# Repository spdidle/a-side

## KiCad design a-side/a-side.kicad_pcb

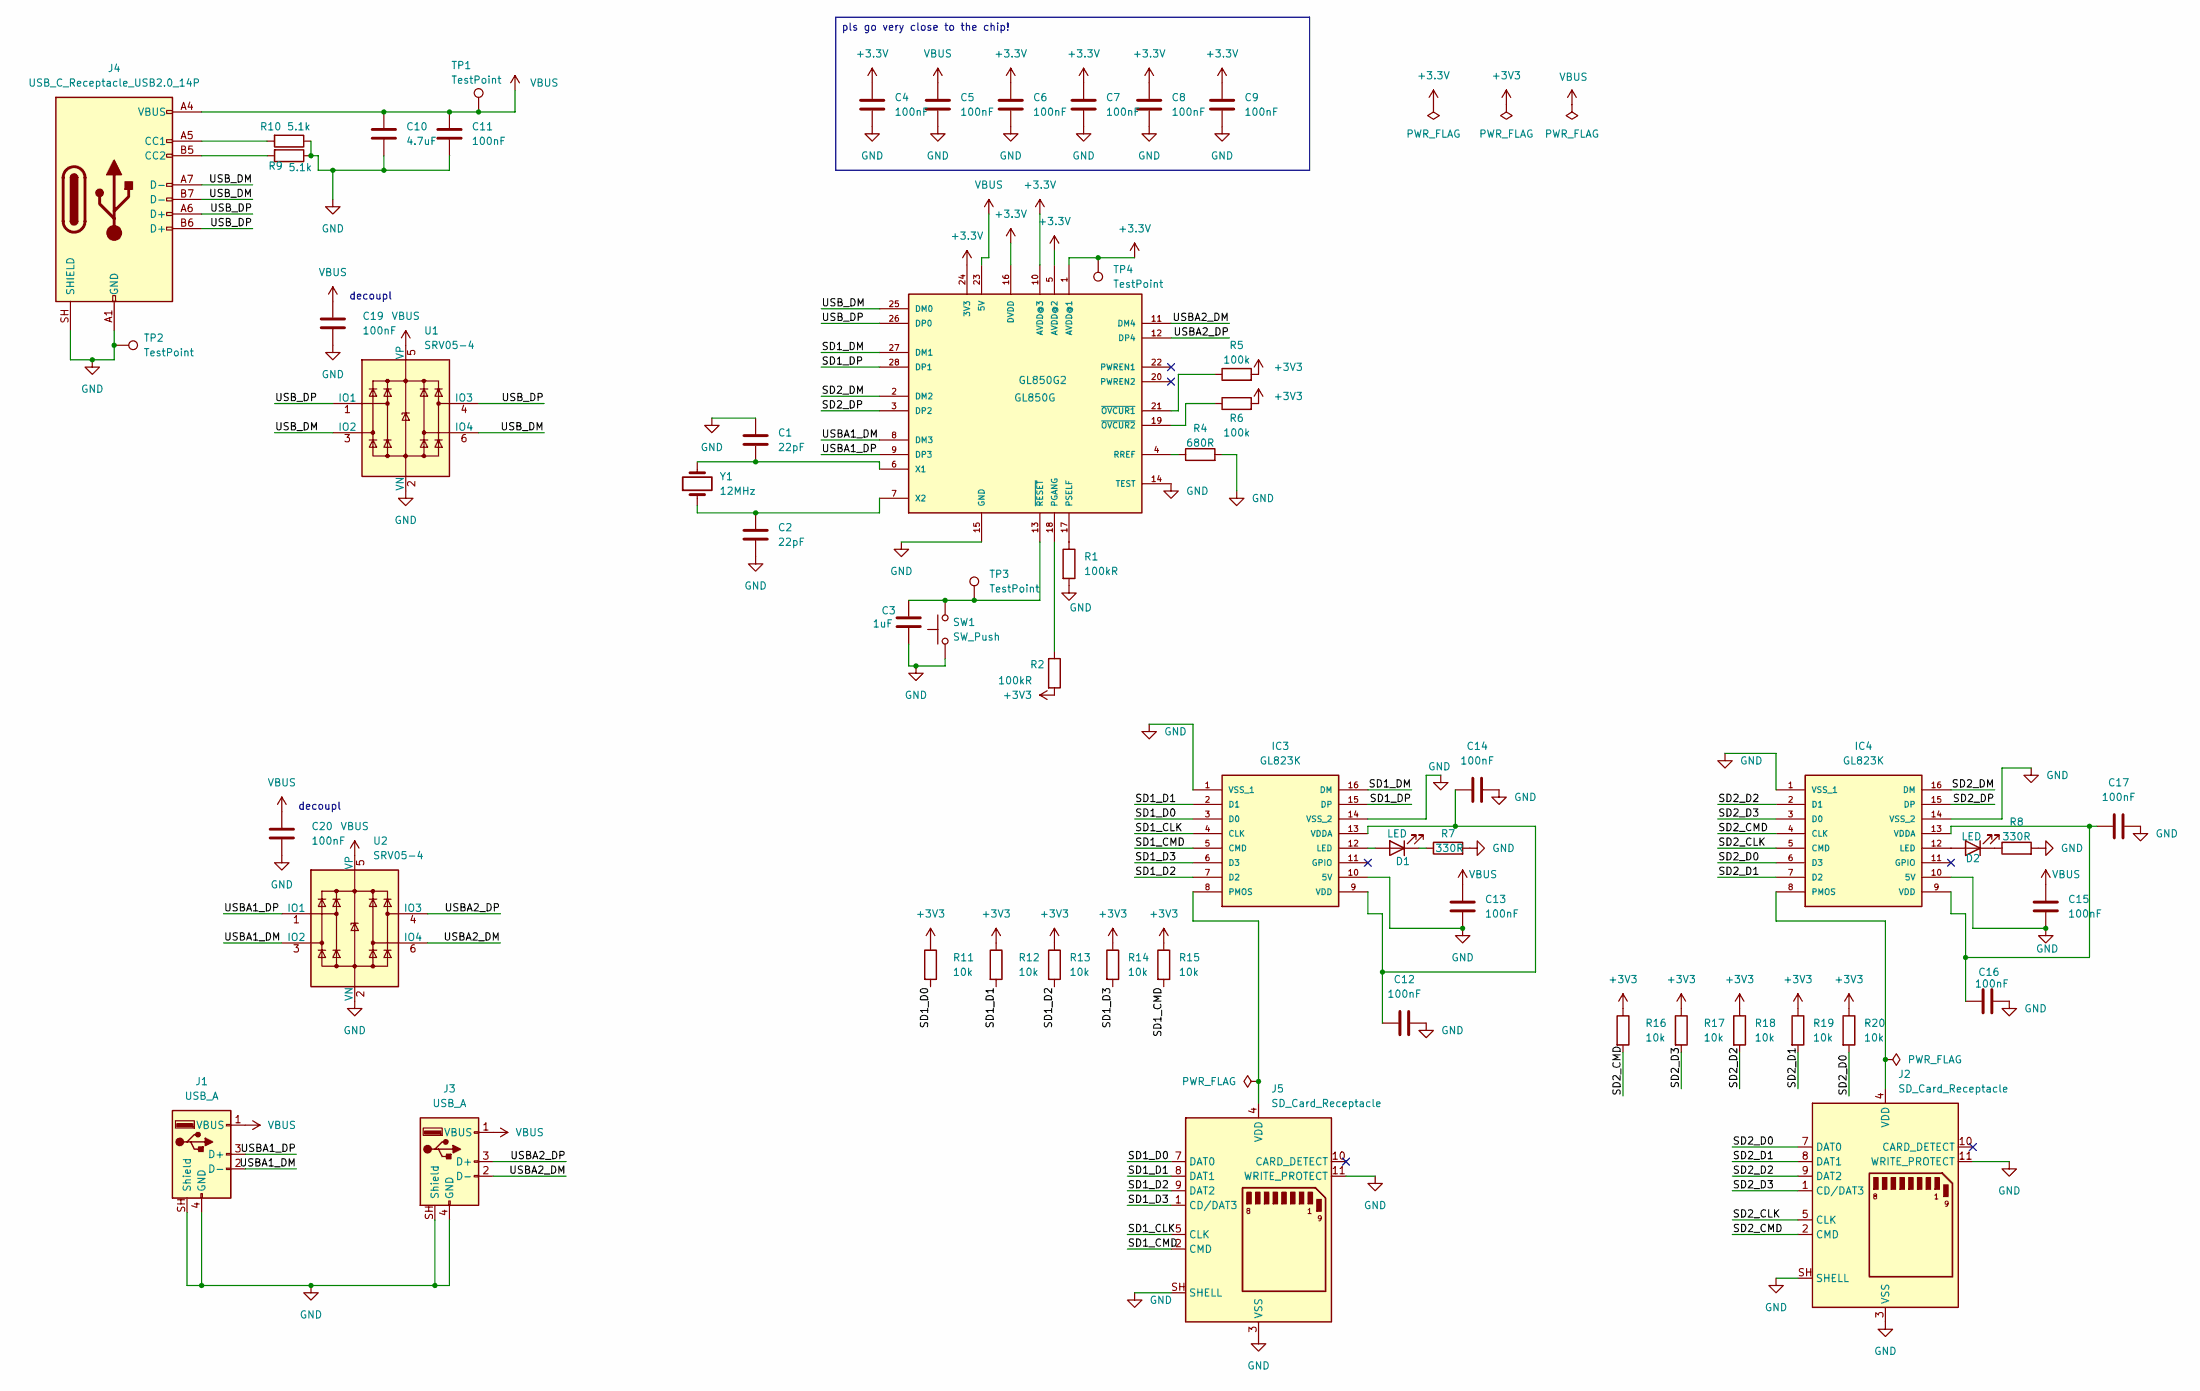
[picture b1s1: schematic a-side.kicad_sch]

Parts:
C1, C2: 22pF; C_0805_2012Metric
C3: 1uF; C_0805_2012Metric
C4, C5, C6, C7, C8, C9, C11, C12, C13, C14, C15, C16, C17, C19, C20: 100nF; C_0805_2012Metric
C10: 4.7uF; C_0805_2012Metric
D1, D2: LED; LED_0805_2012Metric_Pad1.15x1.40mm_HandSolder
GL850G2: GL850G; 28SSOP
IC3, IC4: GL823K; SOP64P600X175-16N; MANUFACTURER_PART_NUMBER GL823K
J1, J3: USB_A; USB_A_Connfly_DS1098_Horizontal
J2, J5: SD_Card_Receptacle; SD_Kyocera_145638009511859+
J4: USB_C_Receptacle_USB2.0_14P; USB_C_Receptacle_HRO_TYPE-C-31-M-12
R1, R2: 100kR; R_0805_2012Metric
R4: 680R; R_0805_2012Metric
R5, R6: 100k; R_0805_2012Metric
R7, R8: 330R; R_0805_2012Metric
R9, R10: 5.1k; R_0805_2012Metric
R11, R12, R13, R14, R15, R16, R17, R18, R19, R20: 10k; R_0805_2012Metric
SW1: SW_Push; SW_Push_SPST_NO_Alps_SKRK
TP1, TP2, TP3, TP4: TestPoint; TestPoint_Pad_D1.0mm
U1, U2: SRV05-4; SOT-23-6
Y1: 12MHz; Crystal_SMD_3225-4Pin_3.2x2.5mm_HandSoldering

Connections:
+3.3V: C4.1, C6.1, C7.1, C8.1, C9.1, GL850G2.1 (AVDD@1), GL850G2.5 (AVDD@2), GL850G2.10 (AVDD@3), GL850G2.16 (DVDD), GL850G2.24 (3V3), TP4.1 (1_1)
+3V3: R2.2, R5.2, R6.2, R11.1, R12.1, R13.1, R14.1, R15.1, R16.1, R17.1, R18.1, R19.1, R20.1
/SD1_CLK: IC3.4 (CLK), J5.5 (CLK)
/SD1_CMD: IC3.5 (CMD), J5.2 (CMD), R15.2
/SD1_D0: IC3.3 (D0), J5.7 (DAT0), R11.2
/SD1_D1: IC3.2 (D1), J5.8 (DAT1), R12.2
/SD1_D2: IC3.7 (D2), J5.9 (DAT2), R13.2
/SD1_D3: IC3.6 (D3), J5.1 (CD/DAT3), R14.2
/SD1_DM: GL850G2.27 (DM1), IC3.16 (DM)
/SD1_DP: GL850G2.28 (DP1), IC3.15 (DP)
/SD2_CLK: IC4.5 (CMD), J2.5 (CLK)
/SD2_CMD: IC4.4 (CLK), J2.2 (CMD), R16.2
/SD2_D0: IC4.6 (D3), J2.7 (DAT0), R20.2
/SD2_D1: IC4.7 (D2), J2.8 (DAT1), R19.2
/SD2_D2: IC4.2 (D1), J2.9 (DAT2), R18.2
/SD2_D3: IC4.3 (D0), J2.1 (CD/DAT3), R17.2
/SD2_DM: GL850G2.2 (DM2), IC4.16 (DM)
/SD2_DP: GL850G2.3 (DP2), IC4.15 (DP)
/USBA1_DM: GL850G2.8 (DM3), J1.2 (D-), U2.3 (IO2)
/USBA1_DP: GL850G2.9 (DP3), J1.3 (D+), U2.1 (IO1)
/USBA2_DM: GL850G2.11 (DM4), J3.2 (D-), U2.6 (IO4)
/USBA2_DP: GL850G2.12 (DP4), J3.3 (D+), U2.4 (IO3)
/USB_DM: GL850G2.25 (DM0), J4.A7 (D-), J4.B7 (D-), U1.3 (IO2), U1.6 (IO4)
/USB_DP: GL850G2.26 (DP0), J4.A6 (D+), J4.B6 (D+), U1.1 (IO1), U1.4 (IO3)
GND: C1.1, C2.2, C3.1, C4.2, C5.2, C6.2, C7.2, C8.2, C9.2, C10.1, C11.2, C12.2, C13.2, C14.2, C15.2, C16.2, C17.2, C19.2, C20.2, GL850G2.14 (TEST), GL850G2.15 (GND), IC3.1 (VSS_1), IC3.10 (5V), IC3.14 (VSS_2), IC4.1 (VSS_1), IC4.10 (5V), IC4.14 (VSS_2), J1.4 (GND), J1.SH (Shield), J2.3 (VSS), J2.6 (VSS), J2.11 (WRITE_PROTECT), J2.SH (SHELL), J3.4 (GND), J3.SH (Shield), J4.A1 (GND), J4.A12 (GND), J4.B1 (GND), J4.B12 (GND), J4.SH (SHIELD), J5.3 (VSS), J5.6 (VSS), J5.11 (WRITE_PROTECT), J5.SH (SHELL), R1.2, R4.2, R7.2, R8.2, R9.1, R10.1, SW1.1, TP2.1 (1_1), U1.2 (VN), U2.2 (VN)
unnamed: D1.2 (A), IC3.12 (LED)
unnamed: D1.1 (K), R7.1
unnamed: D2.2 (A), IC4.12 (LED)
unnamed: D2.1 (K), R8.1
unnamed: GL850G2.18 (PGANG), R2.1
unnamed: GL850G2.17 (PSELF), R1.1
unnamed: GL850G2.4 (RREF), R4.1
unnamed: C1.2, GL850G2.6 (X1), Y1.2
unnamed: C2.1, GL850G2.7 (X2), Y1.1
unnamed: GL850G2.21 (~OVCUR1), R5.1
unnamed: GL850G2.19 (~OVCUR2), R6.1
unnamed: C3.2, GL850G2.13 (~RESET), SW1.2, TP3.1 (1_1)
unnamed: IC3.8 (PMOS), J5.4 (VDD)
unnamed: C12.1, C14.1, IC3.9 (VDD), IC3.13 (VDDA)
unnamed: IC4.8 (PMOS), J2.4 (VDD)
unnamed: C16.1, C17.1, IC4.9 (VDD), IC4.13 (VDDA)
unnamed: J4.A5 (CC1), R10.2
unnamed: J4.B5 (CC2), R9.2
VBUS: C5.1, C10.2, C11.1, C13.1, C15.1, C19.1, C20.1, GL850G2.23 (5V), J1.1 (VBUS), J3.1 (VBUS), J4.A4 (VBUS), J4.A9 (VBUS), J4.B4 (VBUS), J4.B9 (VBUS), TP1.1 (1_1), U1.5 (VP), U2.5 (VP)

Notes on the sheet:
decoupl
pls go very close to the chip!

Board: 2 copper layers, 56 parts (0 on the bottom side), 44 nets, no tracks yet.

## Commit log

2026-04-05 start
    started working icl. this is such a drag so i finished my schematic and its time to clear my 36 drc violations ig 🥰
2026-04-13 oops cant forget to commit!
    soo mostly just about finished my pcb schema? waiting on some of the errors to fix themselves (jk, ill do it tmrw) and assigning footprints tonight and ill do 1 more commit in a bit :)
2026-04-13 schema done! (kinda)
    gonna start fixing erors tomorrow and layout tmrw but yay shcema is 99% mostly kinda done! yay! yay! yay!!! 😸
2026-04-13 oops
    accidentally left out a few files whoops
2026-04-14 sorrryyy
    this is a commit from last night, started layout, fixed schematic issues and well. ready to fix problems now
2026-04-14 comitttt
    fixed most of the problems stated yesterday, NC's on your ESD protection is a red flag, VCC and differentials should bridge the 2 ESD pins
    C3 and C18 aren't done properly and should be in parallel to the AMS1117
    All my footprints are buns and not from KiCad library
    SD data pins are wired to the mounting pins...
    And I should probably consider not using a connector for the upstream but rather a usbc-usbc wire to connect the two.
    YEAH WHATEVER JUST IGNORE THAT theyre mostly fineeee ig ill go home and finish.
2026-04-15 small worksesh
    finishweed my test earlier decided to get some work (NOT) done. scoured the internet for a footprint and i think i found one chat, gonna add it after studying
2026-04-17 work !!
    fixingmostly schematic and stuff yay still working
2026-06-10 yea i WISH something changed
    but i dont really think it did
2026-06-13 yayyy done schema
    :P
2026-06-13 give up on schematic
    im tired i need sleep
